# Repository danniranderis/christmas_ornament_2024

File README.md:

# Christmas Ornament 2024
This year marks the second time creating an electronics project for the Christmas holidays.  
The pcb resembles a Christmas ornament-ball in red with silkscreen and LEDs for a twinkling star effect.

## Hardware
The "Hardware" directory within this repository contains PCB design as a KiCAD 8.0 project.

## Firmware
The "Firmware" directory within this repository contains the firmware for the ATtiny13 MCU as an Arduino project.
This utilizes the [Microcore](https://github.com/MCUdude/MicroCore) hardware package.

## Documentation
The "Documentation" directory within this repository contains various documentation-files for the project. Find PDFs, images and alike herewithin.

## Credits
- Danni Randeris <danni@danniranderis.dk>

## License
Copyright 2024 Danni Randeris

This project is licensed under the TAPR Open Hardware License (www.tapr.org/OHL). The "license" folder within this repository contains a copy of this license in plain text format.

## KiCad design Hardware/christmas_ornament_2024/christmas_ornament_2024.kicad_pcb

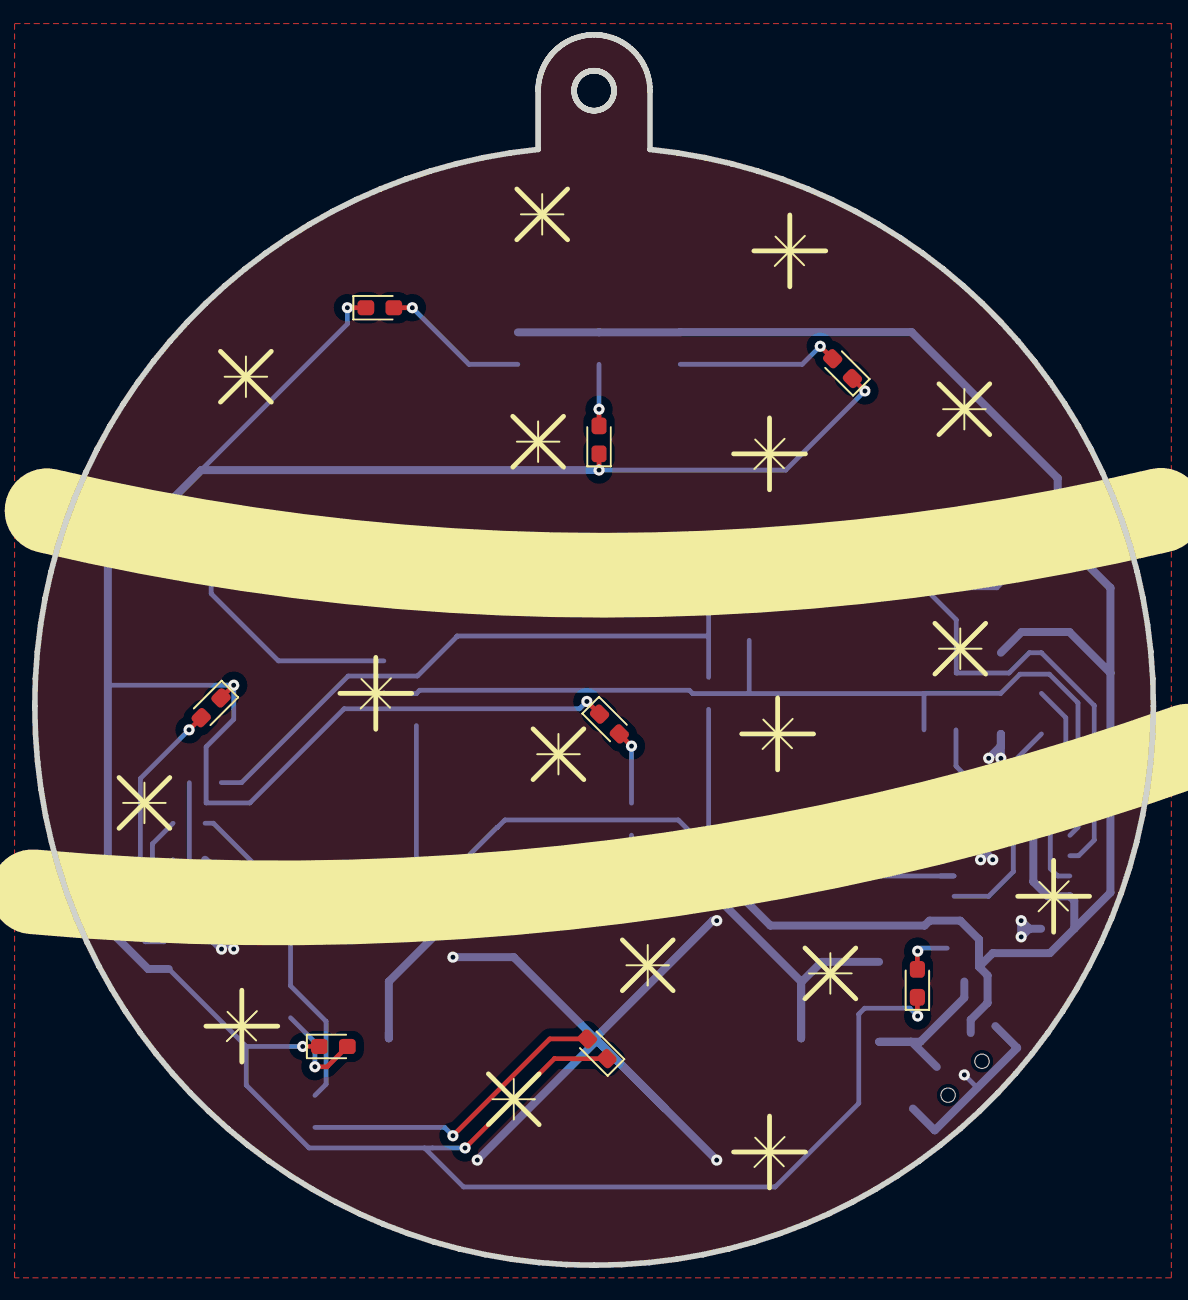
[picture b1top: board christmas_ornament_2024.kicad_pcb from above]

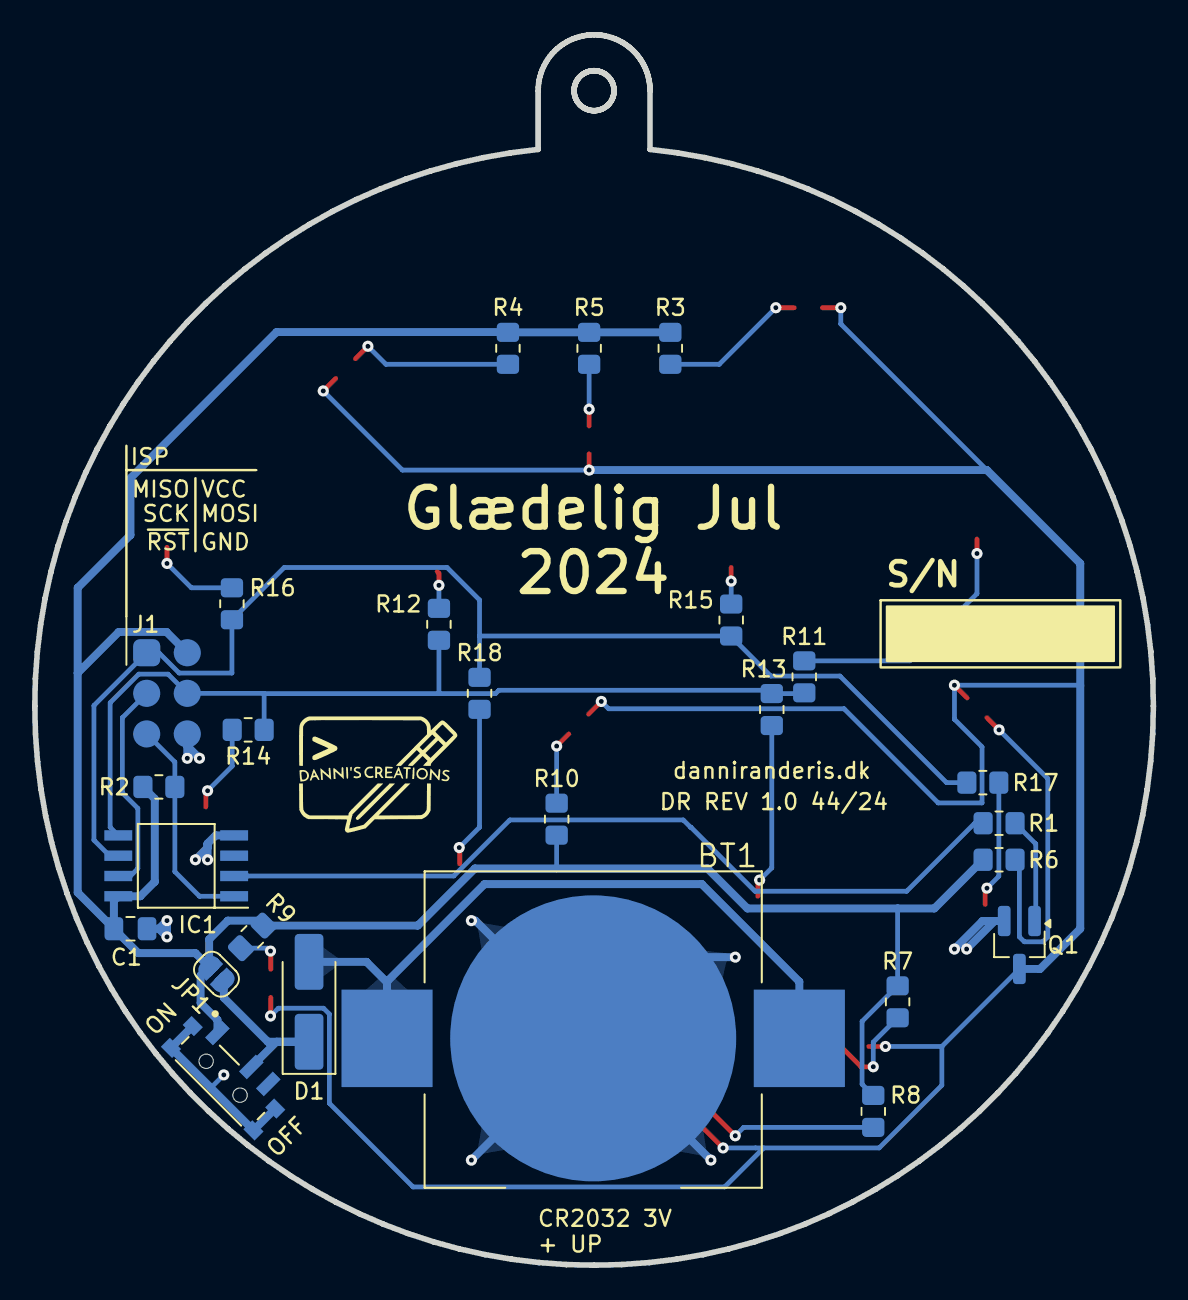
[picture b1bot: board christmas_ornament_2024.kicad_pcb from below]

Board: 2 copper layers, 70.0 x 77.0 mm, 59 parts (26 on the bottom side), 27 nets.

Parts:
BT1: CR2032 3V; BAT_BAT-HLD-003-SMT
C1: 100n; C_0805_2012Metric_Pad1.18x1.45mm_HandSolder
D1: SS12; D_SMA_Handsoldering
D2, D3, D4, D5, D6, D7, D8, D9, D10, D11, D12, D13, D14, D15, D16, D17: LED; LED_0603_1608Metric_Pad1.05x0.95mm_HandSolder
IC1: ATTINY13V-10SU; SOIC127P798X216-8N
J1: ISP Header; ISP_Pad
JP1: SWT_bypass; SolderJumper-2_P1.3mm_Open_RoundedPad1.0x1.5mm
Q1: MMBT3904; SOT-23_Handsoldering
R1: 2k2; R_0805_2012Metric_Pad1.20x1.40mm_HandSolder
R2: 10k; R_0805_2012Metric_Pad1.20x1.40mm_HandSolder
R3, R4, R5, R6, R7, R8, R9, R10, R11, R12, R13, R14, R15, R16, R17, R18: 470; R_0805_2012Metric_Pad1.20x1.40mm_HandSolder
SW1: PCM12SMTR; SW_PCM12SMTR
U1, U2, U3, U4, U5, U6, U7, U10, U11, U12, U13, U14, U15, U16, U17, U18, U19: star

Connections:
+3V: C1.1, IC1.8 (VCC), J1.2 (VCC), JP1.2 (B), R2.1, R3.1, R4.1, R5.1, R6.1, R7.1, R8.1, R9.1, R10.1, SW1.1
/LED_Bank_1: IC1.2 ((PCINT3/CLKI/ADC3)_PB3), R1.2
/LED_Bank_2_MOSI: IC1.5 (PB0_(MOSI/AIN0/OC0A/PCINT0)), J1.4 (MOSI), R11.1, R12.1, R13.1, R14.1
/LED_Bank_3_MISO: IC1.6 (PB1_(MISO/AIN1/OC0B/INT0/PCINT1)), J1.1 (MISO), R15.1, R16.1, R17.1, R18.1
/RST: IC1.1 ((PCINT5/~RESET/ADC0/DW)_PB5), J1.5 (~RST), R2.2
/SCK: IC1.7 (PB2_(SCK/ADC1/T0/PCINT2)), J1.3 (SCK)
DARAN_GND: BT1.N, C1.2, D10.1 (K), D11.1 (K), D12.1 (K), D13.1 (K), D14.1 (K), D15.1 (K), D16.1 (K), D17.1 (K), IC1.4 (GND), J1.6 (GND), Q1.2 (E), SW1.S1 (SHIELD), SW1.S2 (SHIELD), SW1.S3 (SHIELD), SW1.S4 (SHIELD)
unnamed: BT1.P1, BT1.P2, D1.2 (A)
unnamed: D1.1 (K), JP1.1 (A), SW1.2
unnamed: D2.2 (A), R3.2
unnamed: D2.1 (K), D3.1 (K), D4.1 (K), D5.1 (K), D6.1 (K), D7.1 (K), D8.1 (K), D9.1 (K), Q1.3 (C)
unnamed: D3.2 (A), R4.2
unnamed: D4.2 (A), R5.2
unnamed: D5.2 (A), R6.2
unnamed: D6.2 (A), R7.2
unnamed: D7.2 (A), R8.2
unnamed: D8.2 (A), R9.2
unnamed: D9.2 (A), R10.2
unnamed: D10.2 (A), R11.2
unnamed: D11.2 (A), R12.2
unnamed: D12.2 (A), R13.2
unnamed: D13.2 (A), R14.2
unnamed: D14.2 (A), R15.2
unnamed: D15.2 (A), R16.2
unnamed: D16.2 (A), R17.2
unnamed: D17.2 (A), R18.2
unnamed: Q1.1 (B), R1.1

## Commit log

2024-10-12 Initializing project
2024-12-20 Commiting files to repo.
